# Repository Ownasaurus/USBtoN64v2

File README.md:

# USBtoN64v2
Utilizes STM32F446 on a Nucleo-F446RE with custom header or on a fully custom board for usb and n64 communication.

In this repository, you can find the latest version of the source code (TrueSTUDIO), 3D case (.stl), and PCB (Eagle .brd and .sch) files.

Currently supported USB devices:
- Keyboard
- Dualshock 3 Sixaxis
- Dualshock 4 v1 (with help from Kazon Wilson [kwilson21]) and v2
- Wireless Xbox 360 with Microsoft USB wireless receiver
- Wired Xbox 360
- Wired Xbox One

## Setting the controls:
1) Press the blue button on the Nucleo or the only button on the custom PCB. A new green LED (light) should light up solid when you go into "set controls" mode, and it should turn off when you finish setting the controls correctly.
2) Press the buttons in the appropriate order depending on which device is plugged in. For Xbox and PS, you also need to set range and deadzone. Please see below for instructions.
3) (optional) Press the same button again at any time to exit “set controls” mode early if you make a mistake.

### Xbox / Playstation:
DPAD_UP, DPAD_DOWN, DPAD_LEFT, DPAD_RIGHT, BUTTON_START, BUTTON_B, BUTTON_A, C_UP, C_DOWN, C_LEFT, C_RIGHT, BUTTON_L, BUTTON_R, BUTTON_Z

Next you set your RANGE. It starts at 100 by default.
Up (+) and Down (-) on the D-pad will increase or decrease the range by 5.
Right (+) and Left (-) on the D-pad will increase or decrease the range by 1.
The range cannot be greater than 100 or less than 0.
When you are done, hit "A" on the Xbox controller or "X" on the Playstation controller to move on.

Next you set your DEADZONE. It starts at 20 by default.
Up (+) and Down (-) on the D-pad will increase or decrease the deadzone by 5.
Right (+) and Left (-) on the D-pad will increase or decrease the deadzone by 1.
The deadzone cannot be greater than 100 or less than 0.
When you are done, hit "A" on the Xbox controller or "X" on the Playstation controller. Congratulations, you are done configuring your controls!

### KB:
A_UP, A_DOWN, A_LEFT, A_RIGHT, DPAD_UP, DPAD_DOWN, DPAD_LEFT, DPAD_RIGHT, BUTTON_START, BUTTON_B, BUTTON_A, C_UP, C_DOWN, C_LEFT, C_RIGHT, BUTTON_L, BUTTON_R, BUTTON_Z

Note that the device saves the controls even when the device is powered off. It saves the Xbox and Playstation controls together as a shared layout and the Keyboard controls separately.

## Updating the firmware:

### Nucleo (Prototype consisting of 2 connected boards)
Plug the device into a PC with a USB mini B cable, and drag&drop a .bin firmware file.

### v2 (one board in a case distributed only after 09/2018)
The v2 has a switch with two possible positions: "ON" or "1" (which is qutie confusing if you ask me).
- *The switch should be set to "1" for normal operation.*
- *The switch should be set to "ON" for firmware upgrade.*
- *The switch should be never be flipped while the device is powered to "ON" for firmware upgrade.*

So, first fip the switch to "ON". Plug the device into a PC with a USB mini B cable, and it should show up as a USB DFU device.
Use the "DfuSeDemo" software provided by STMicroelectronics to update the firmware with a .dfu file.
The "Dfu file manager" software is also provided alongside the "DfuSeDemo" by STMicroelectronics.
Then, unplug the device from the PC. Finally, flip the switch back "1".

## TODO:
- Complete LED support for PS4 (currently non-functional)
- Re-design PCB (and case) to be significantly smaller (in progress)

## Currently known bugs:
- None!

By: Ownasaurus

## Special thanks to:
????? ????? [Rainshifter] for help and support along the whole process

Kazon Wilson [kwilson21] for help with Dualshock 4 support

???? ????? [Serisium] for help with PCB design and understanding the STM32 hardware

Jeff Longo [?????] for help with PCB design and 3D case design

# Gamecube support - ALPHA
Gamecube support is currently in the experimental phase.
- If the data line and ground lines of a Gamecube cable are connected to the adapter, it should function.
- If BOTH N64 and Gamecube cables are attached, the device should be able to automatically detect which console is being used. The unused cable MUST be unplugged for proper functionality.
- Only XBOX controllers are currently supported.
- The controls are currently static and mimic the Gamecube controller layout.
- The sensitivity and deadzone are "borrowed" from the N64 controller settings.
- GC(X) / XBOX(B) button is currently un-mapped due to Rainshifter's preferences for bug testing.

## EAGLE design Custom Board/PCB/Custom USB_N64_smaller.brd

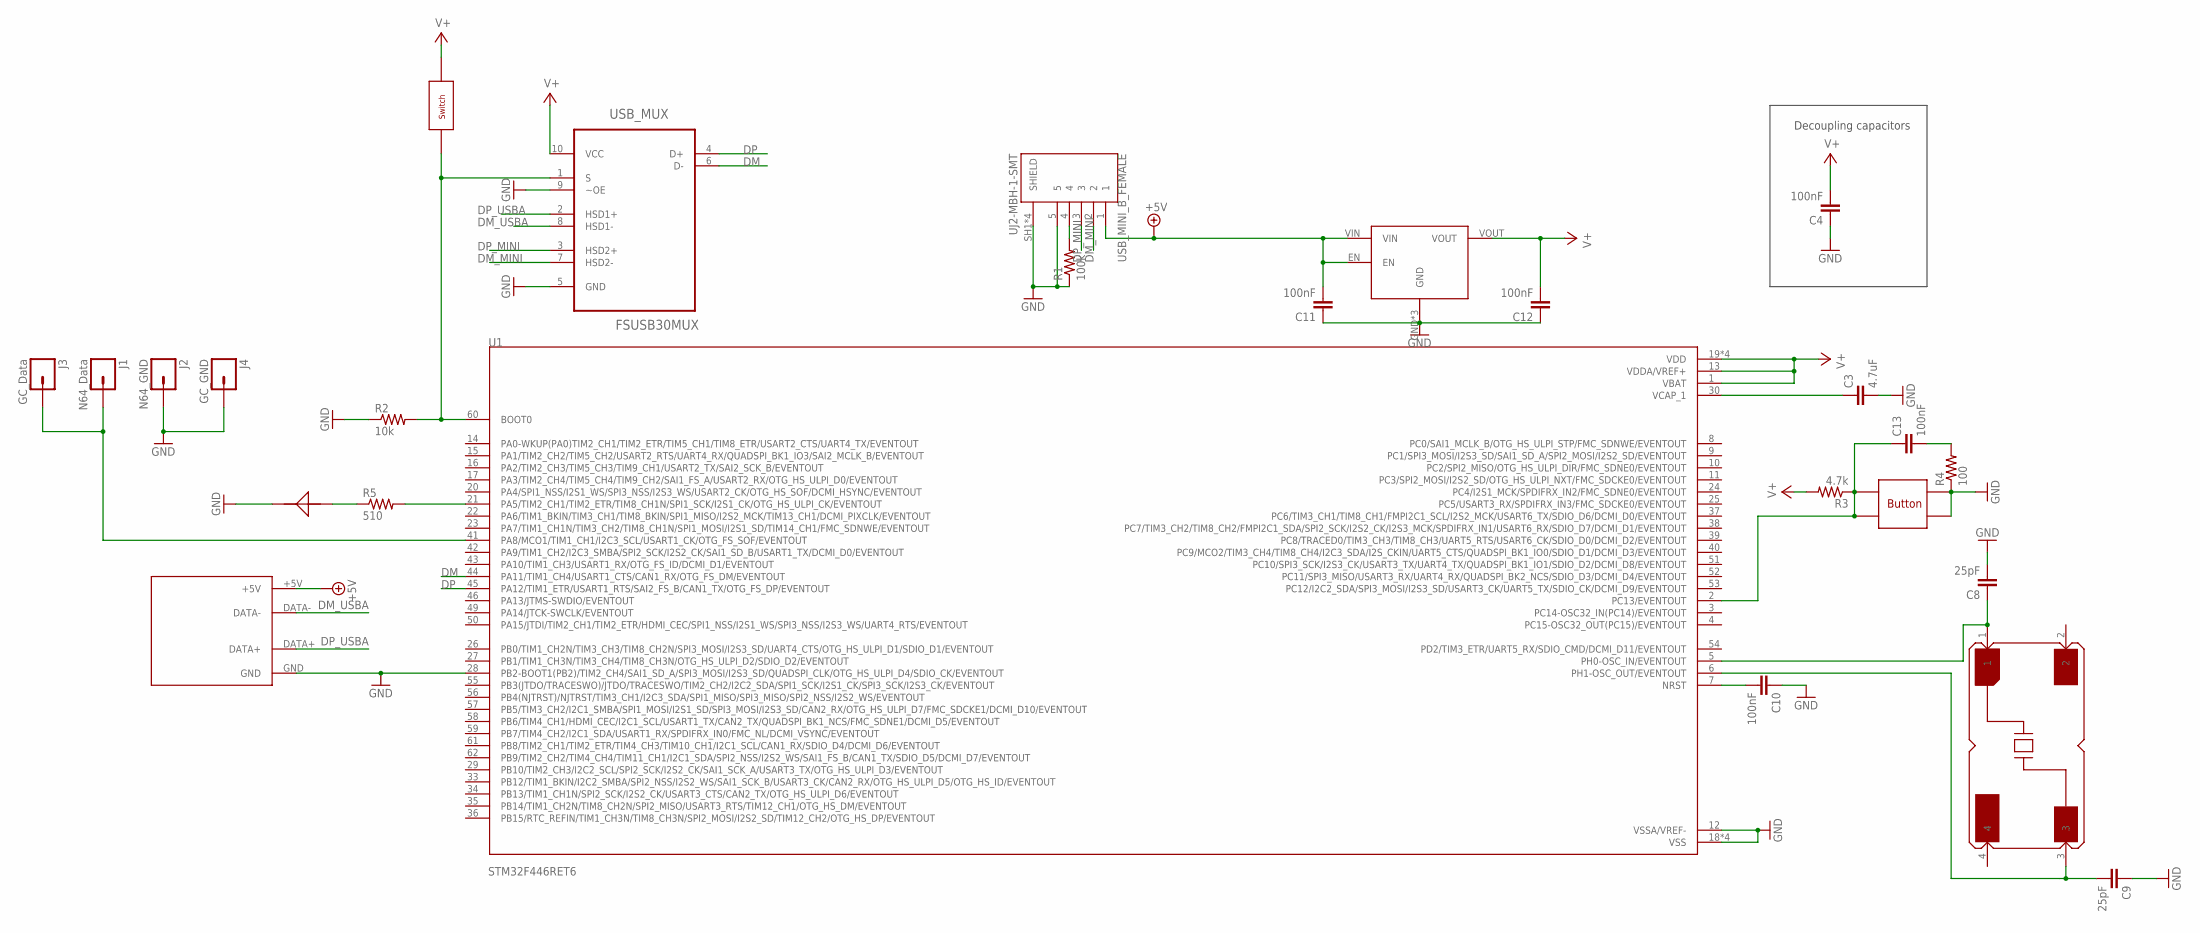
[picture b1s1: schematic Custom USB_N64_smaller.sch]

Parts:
C3: 4.7uF; C0805
C4, C10, C11, C12, C13: 100nF; C0805
C8, C9: 25pF; C0805
CHANGE_CONTROLS: PUSHBUTTON
J1: N64_Data; 1X01
J2: N64_GND; 1X01
J3: GC_Data; 1X01
J4: GC_GND; 1X01
R1: 100k; R0805
R2: 10k; R0805
R3: 4.7k; R0805
R4: 100; R0805
R5: 510; R0805
SWITCH: DM01
U1: STM32F446RET6; QFP50P1200X1200X160-64N
U$6: 17-21SYGC/S530-E2/TR8
USB_A_FEMALE: USB_A_F
USB_MINI_B_FEMALE: UJ2-MBH-1-SMT; CUI_UJ2-MBH-1-SMT
USB_MUX: FSUSB30MUX; SOP50P490X110-10N
V_REG: S-1172B33-U5T1G
XTAL_HSE: ABMM-8.000MHZ-B2-T; DFN-4

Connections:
3V3: C4.2, C12.2, R3.2, SWITCH.P$1, U1.1 (VBAT), U1.13 (VDDA/VREF+), U1.19 (VDD), U1.32 (VDD), U1.48 (VDD), U1.64 (VDD), USB_MUX.10 (VCC), V_REG.VOUT
+5V: C11.2, USB_A_FEMALE.+5V, USB_MINI_B_FEMALE.1, V_REG.EN, V_REG.VIN
DM: U1.44 (PA11/TIM1_CH4/USART1_CTS/CAN1_RX/OTG_FS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), USB_MUX.6 (D-)
DM_MINI: USB_MINI_B_FEMALE.2, USB_MUX.7 (HSD2-)
DM_USBA: USB_A_FEMALE.DATA-, USB_MUX.8 (HSD1-)
DP: U1.45 (PA12/TIM1_ETR/USART1_RTS/SAI2_FS_B/CAN1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), USB_MUX.4 (D+)
DP_MINI: USB_MINI_B_FEMALE.3, USB_MUX.3 (HSD2+)
DP_USBA: USB_A_FEMALE.DATA+, USB_MUX.2 (HSD1+)
GND: C3.2, C4.1, C8.2, C9.1, C10.1, C11.1, C12.1, CHANGE_CONTROLS.P$3, CHANGE_CONTROLS.P$4, J2.1, J4.1, R1.1, R2.1, R4.1, U1.12 (VSSA/VREF-), U1.18 (VSS), U1.28 (PB2-BOOT1(PB2)/TIM2_CH4/SAI1_SD_A/SPI3_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), U1.31 (VSS), U1.47 (VSS), U1.63 (VSS), U$6.NEG, USB_A_FEMALE.GND, USB_MINI_B_FEMALE.5, USB_MINI_B_FEMALE.SH1 (SHIELD), USB_MINI_B_FEMALE.SH2 (SHIELD), USB_MINI_B_FEMALE.SH3 (SHIELD), USB_MINI_B_FEMALE.SH4 (SHIELD), USB_MUX.5 (GND), USB_MUX.9 (~OE), V_REG.GND, V_REG.GND2 (GND), V_REG.GND3 (GND)
unnamed: R2.2, SWITCH.P$2, U1.60 (BOOT0), USB_MUX.1 (S)
unnamed: C10.2, U1.7 (NRST)
unnamed: C8.1, U1.5 (PH0-OSC_IN/EVENTOUT), XTAL_HSE.1
unnamed: C3.1, U1.30 (VCAP_1)
unnamed: C9.2, U1.6 (PH1-OSC_OUT/EVENTOUT), XTAL_HSE.3
unnamed: J1.1, J3.1, U1.41 (PA8/MCO1/TIM1_CH1/I2C3_SCL/USART1_CK/OT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)
unnamed: C13.1, CHANGE_CONTROLS.P$1, CHANGE_CONTROLS.P$2, R3.1, U1.2 (PC13/EVENTOUT)
unnamed: R5.2, U1.21 (PA5/TIM2_CH1/TIM2_ETR/TIM8_CH1N/SPI1_SC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)
unnamed: C13.2, R4.2
unnamed: R5.1, U$6.POS
unnamed: R1.2, USB_MINI_B_FEMALE.4

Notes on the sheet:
Decoupling capacitors

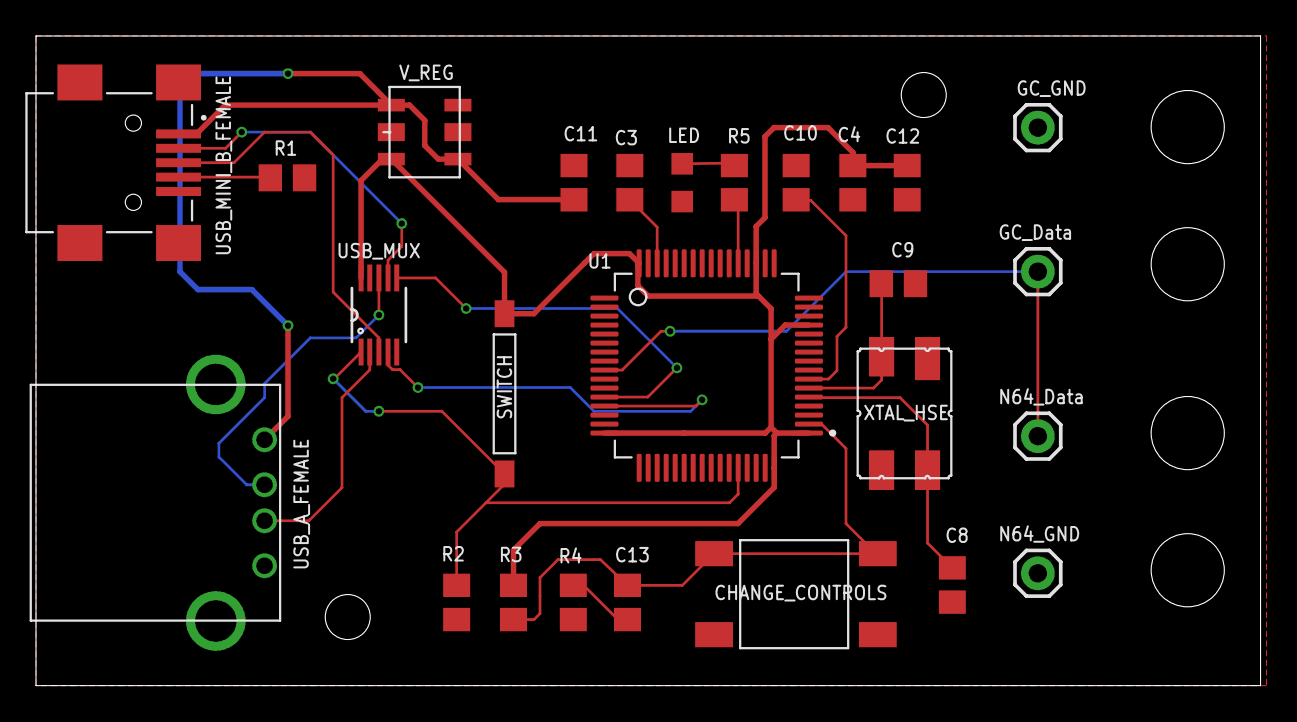
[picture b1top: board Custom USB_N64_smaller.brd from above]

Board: 2 copper layers, 68.0 x 36.1 mm, 26 parts (0 on the bottom side), 20 nets.

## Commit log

2018-07-24 initial commit with working N64 communication
2018-07-30 initial dualshock3 functionality
2018-07-30 Updated README. indicated early KB and PS3 support
2018-08-05 Resolved n64 communication bugs. Skeleton code for XPAD.
2018-08-07 works with wired x360
2018-08-12 xpad family supported, bug fixes, change xpad controls on the fly
2018-08-13 change kb controls on the fly
2018-08-13 updated README to include instructions on setting controls
2018-08-13 fixed bug: xbox one triggers not functioning properly
2018-08-13 All controller types can re-map button layout on-the-fly
2018-08-13 fixed typo in readme and updated release binary
2018-08-13 fixed ps3 led; updated readme; project is now in beta
2018-08-16 fixed wireless x360 issues
2018-08-22 range and sensitivity can now be set by the xbox and playstation users on the fly
2018-08-25 fixed ds3 controller, which apparently broke in a previous patch
2018-08-28 disabled unused pins to increase power efficiency
2018-09-01 Dualshock 4 support completed
2018-09-09 re-organized project; added files for custom board
2018-09-12 adding new, smaller board layout
2018-09-12 fixed faulty V_REG foorprint and N64 silkscreen
2018-09-22 fixed certain keyboards not working properly
2018-09-24 updated custom case, improved window size and position
2018-10-03 updated README with firmware update instructions
2018-10-13 added support for ds4 slim, which apparently didnt work
2018-11-08 beta gamecube support added with XBOX controllers!
2019-01-13 Updated custom board info
2019-06-24 R analog mapped to C buttons
2019-06-26 fixed inverted C stick issue
2019-08-17 Added static USB KB controls for GC
2019-09-01 default usb keyboard gamecube controls
2019-11-10 major cleanup and fix static GC controls
2019-11-10 made default modifier lshift
2019-11-11 fixed tilt modifier

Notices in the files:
parts and their libraries:
SparkFun-Connectors: Licensing: Creative Commons ShareAlike 4.0 International - https://creativecommons.org/licenses/by-sa/4.0
